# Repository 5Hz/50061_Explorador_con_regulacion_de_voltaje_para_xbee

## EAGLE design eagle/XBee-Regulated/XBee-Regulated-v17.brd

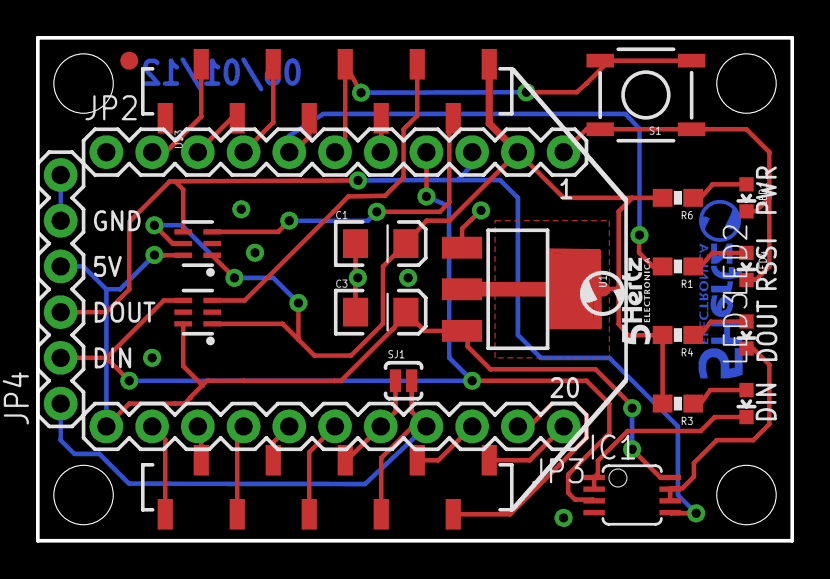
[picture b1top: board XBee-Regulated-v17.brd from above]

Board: 2 copper layers, 41.9 x 27.9 mm, 27 parts (1 on the bottom side), 29 nets.

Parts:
C1, C3: 10uF; EIA3216
IC1: LMV358MMX; MSOP08
JP2, JP3: M11PTH; 1X11
JP4: 1X06
LED1, LED2: Red; LED-0603
LED3, LED4: Green; LED-0603
LOGO2: LOGO_5HZ_H_COOPER_10MM; 5HZ_LOGO_H_COOPER_10MM
LOGO3: LOGO_5HZ_MAIN_5MM; 5HZ_LOGO_MAIN_5MM
R1, R3, R4, R6: 10K; 0603-RES
S1: TACTILE_SWITCH_SMD
SJ1: SOLDERJUMPERNO; SJ_2S-NO
U1: V_REG_NCP1117SMD; SOT223
U$3: XBEE-1B3; XBEE-SMD
U$5, U$9, U$10, U$11: STAND-OFF
U$7, U$12: MAX337; SOT-363
U$16: FIDUCIAL1X2; FIDUCIAL-1X2

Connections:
3.3V: C1.A, JP2.10, R3.2, R4.2, R6.2, U1.2, U$3.1, U$7.1, U$12.1, U$12.5
5V: C3.A, IC1.8, JP3.11, JP4.4, U1.3, U$7.6, U$12.6
CTS: JP3.9, U$3.12
DIN: IC1.3, JP2.8, JP4.2, U$7.4
DIN3: U$3.3, U$7.3
DIO0: JP3.1, U$3.20
DIO1: JP3.2, U$3.19
DIO2: JP3.3, U$3.18
DIO3: JP3.4, JP4.1, SJ1.2, U$3.17
DIO4: JP3.10, U$3.11
DIO5: JP3.6, U$3.15
DIO9: JP3.8, U$3.13
DIO11: JP2.4, U$3.7
DIO12: JP2.7, U$3.4
DOUT: IC1.5, JP2.9, JP4.3, U$12.4
DOUT3: U$3.2, U$12.3
DTR: JP2.2, U$3.9
GND: C1.C, C3.C, IC1.4, JP2.1, JP2.11, JP4.5, JP4.6, LED1.C, LED4.C, S1.1, S1.2, U1.1, U$3.10, U$7.2, U$7.5, U$12.2
unnamed: LED2.A, R4.1
unnamed: LED4.A, R1.1
unnamed: LED3.A, R3.1
unnamed: IC1.6, IC1.7, LED2.C
unnamed: IC1.1, IC1.2, LED3.C
unnamed: LED1.A, R6.1
RES1: JP2.3, U$3.8
RES2: JP3.7, U$3.14
RESET: JP2.6, S1.3, S1.4, U$3.5
RSSI: JP2.5, R1.2, U$3.6
RTS: JP3.5, SJ1.1, U$3.16

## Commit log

2014-01-13 creación
